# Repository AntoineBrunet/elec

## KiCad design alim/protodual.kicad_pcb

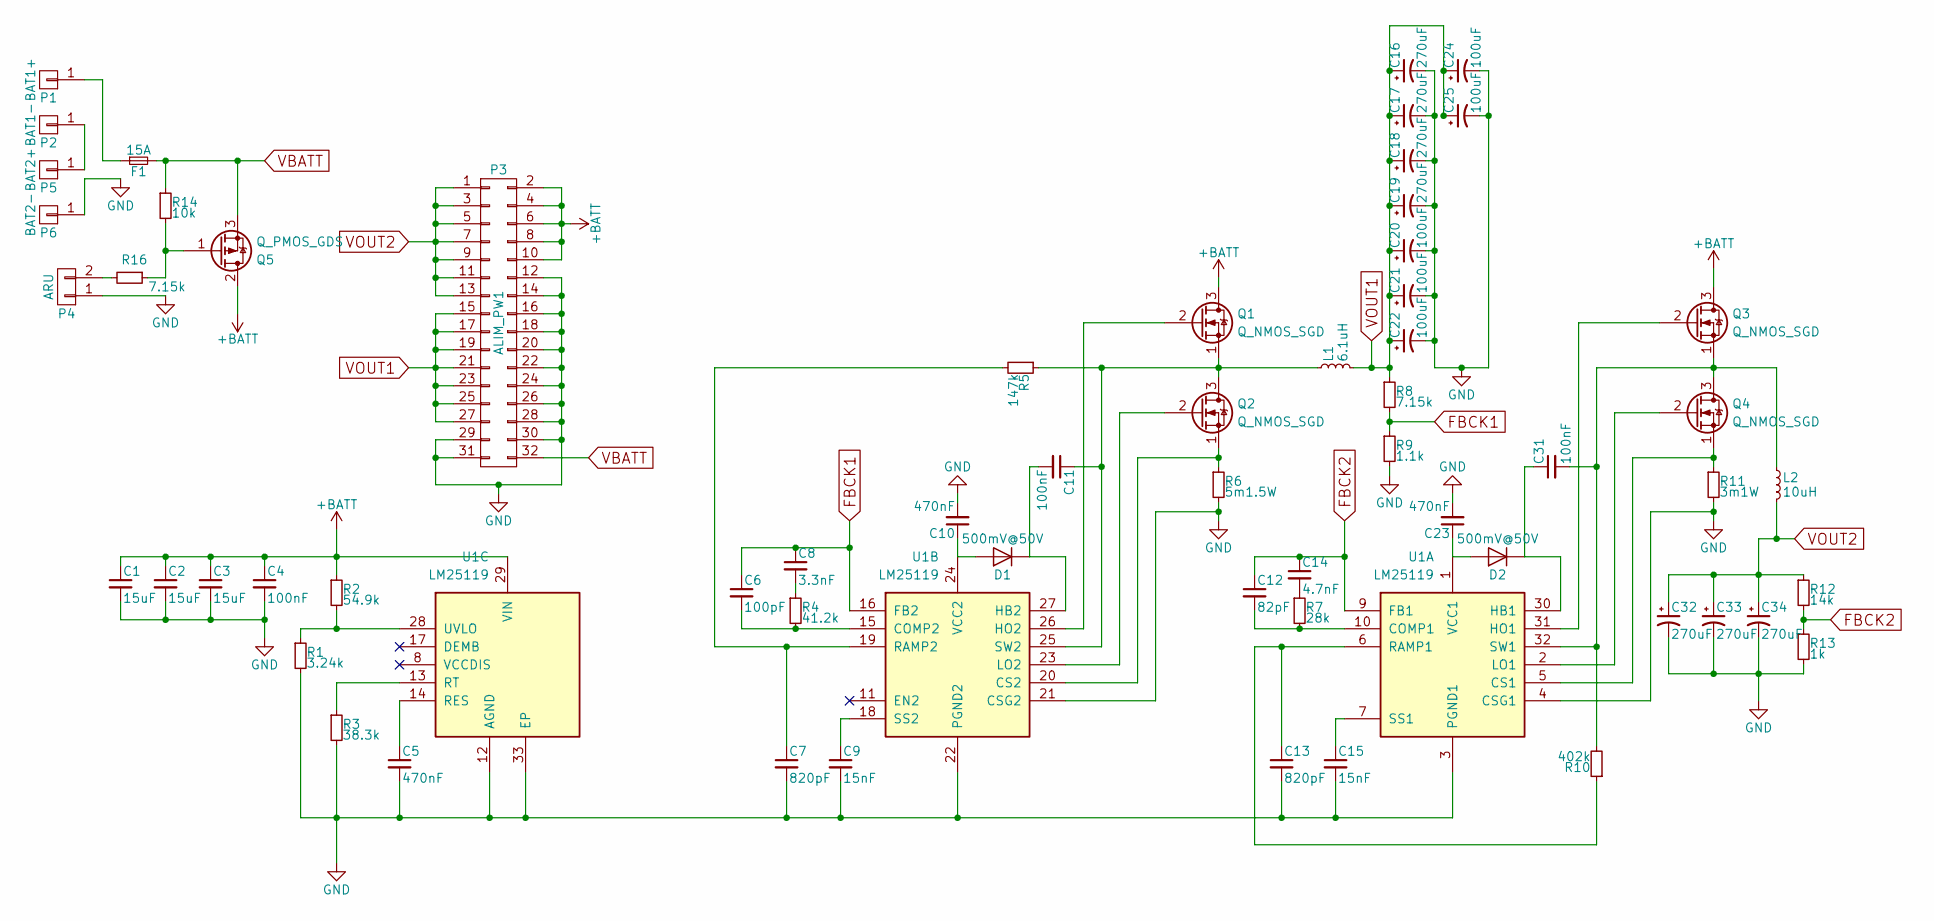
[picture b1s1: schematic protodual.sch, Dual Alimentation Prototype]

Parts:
C1, C2, C3: 15uF; C_2220_HandSoldering
C4, C11, C31: 100nF; C_0603_HandSoldering
C5: 470nF; C_1206_HandSoldering
C6: 100pF; C_0603_HandSoldering
C7, C13: 820pF; C_0603_HandSoldering
C8: 3.3nF; C_0603_HandSoldering
C9, C15: 15nF; C_0805_HandSoldering
C10, C23: 470nF; C_0603_HandSoldering
C12: 82pF; C_0603_HandSoldering
C14: 4.7nF; C_0603_HandSoldering
C16, C17, C18, C19, C32, C33, C34: 270uF; c_elec_6.3x7.7
C20, C21, C22, C24, C25: 100uF; Tantalum_Case-B_EIA-3528-21_Hand
D1, D2: 500mV@50V; D_0805
F1: 15A; Fuseholder5x20_horiz_SemiClosed_Casing10x25mm
L1: 6.1uH; Inductor_Wurth_HCI-1365
L2: 10uH; Inductor_Wurth_HCI-1365
P1: BAT1+; WireConnection_2.50mm
P2: BAT1-; WireConnection_2.50mm
P3: ALIM_PW1; Pin_Header_Straight_2x16
P4: ARU; Socket_Strip_Straight_1x02
P5: BAT2+; WireConnection_2.50mm
P6: BAT2-; WireConnection_2.50mm
Q1, Q2, Q3, Q4: Q_NMOS_SGD; TDSON8_MOSFET
Q5: Q_PMOS_GDS; SOT-428
R1: 3.24k; R_0603_HandSoldering
R2: 54.9k; R_0603_HandSoldering
R3: 38.3k; R_0603_HandSoldering
R4: 41.2k; R_0603_HandSoldering
R5: 147k; R_0603_HandSoldering
R6: 5m1.5W; R_2010_HandSoldering
R7: 28k; R_0603_HandSoldering
R8, R16: 7.15k; R_0603_HandSoldering
R9: 1.1k; R_0603_HandSoldering
R10: 402k; R_0603_HandSoldering
R11: 3m1W; R_2010_HandSoldering
R12: 14k; R_0603_HandSoldering
R13: 1k; R_0603_HandSoldering
R14: 10k; R_0603_HandSoldering
U1: LM25119; QFN-32-1EP_5x5mm_Pitch0.5mm

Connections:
+BATT: C1.1, C2.1, C3.1, C4.1, P3.2, P3.4, P3.6, P3.8, P3.10, Q1.3 (D), Q3.3 (D), Q5.2 (D), R2.1, U1.29 (VIN)
FBCK1: C6.1, C8.1, R8.2, R9.1, U1.16 (FB2)
FBCK2: C12.1, C14.1, R12.2, R13.1, U1.9 (FB1)
GND: C1.2, C2.2, C3.2, C4.2, C5.2, C7.2, C9.2, C10.2, C13.2, C15.2, C16.2, C17.2, C18.2, C19.2, C20.2, C21.2, C22.2, C23.2, C24.2, C25.2, C32.2, C33.2, C34.2, P3.12, P3.14, P3.16, P3.18, P3.20, P3.22, P3.24, P3.26, P3.28, P3.29, P3.30, P3.31, P4.1, P6.1, R1.2, R3.2, R6.2, R9.2, R11.2, R13.2, U1.3 (PGND1), U1.4 (CSG1), U1.12 (AGND), U1.21 (CSG2), U1.22 (PGND2), U1.33 (EP)
unnamed: C5.1, U1.14 (RES)
unnamed: C6.2, R4.2, U1.15 (COMP2)
unnamed: C7.1, R5.2, U1.19 (RAMP2)
unnamed: C8.2, R4.1
unnamed: C9.1, U1.18 (SS2)
unnamed: C10.1, D1.2 (A), U1.24 (VCC2)
unnamed: C11.1, L1.1, Q1.1 (S), Q2.3 (D), R5.1, U1.25 (SW2)
unnamed: C11.2, D1.1 (K), U1.27 (HB2)
unnamed: C12.2, R7.2, U1.10 (COMP1)
unnamed: C13.1, R10.1, U1.6 (RAMP1)
unnamed: C14.2, R7.1
unnamed: C15.1, U1.7 (SS1)
unnamed: C23.1, D2.2 (A), U1.1 (VCC1)
unnamed: C31.1, D2.1 (K), U1.30 (HB1)
unnamed: C31.2, L2.1, Q3.1 (S), Q4.3 (D), R10.2, U1.32 (SW1)
unnamed: F1.1, P1.1
unnamed: P2.1, P5.1
unnamed: P4.2, R16.2
unnamed: Q1.2 (G), U1.26 (HO2)
unnamed: Q2.1 (S), R6.1, U1.20 (CS2)
unnamed: Q2.2 (G), U1.23 (LO2)
unnamed: Q3.2 (G), U1.31 (HO1)
unnamed: Q4.1 (S), R11.1, U1.5 (CS1)
unnamed: Q4.2 (G), U1.2 (LO1)
unnamed: Q5.1 (G), R14.2, R16.1
unnamed: R1.1, R2.2, U1.28 (UVLO)
unnamed: R3.1, U1.13 (RT)
VBATT: F1.2, P3.32, Q5.3 (S), R14.1
VOUT1: C16.1, C17.1, C18.1, C19.1, C20.1, C21.1, C22.1, C24.1, C25.1, L1.2, P3.15, P3.17, P3.19, P3.21, P3.23, P3.25, P3.27, R8.1
VOUT2: C32.1, C33.1, C34.1, L2.2, P3.1, P3.3, P3.5, P3.7, P3.9, P3.11, P3.13, R12.1

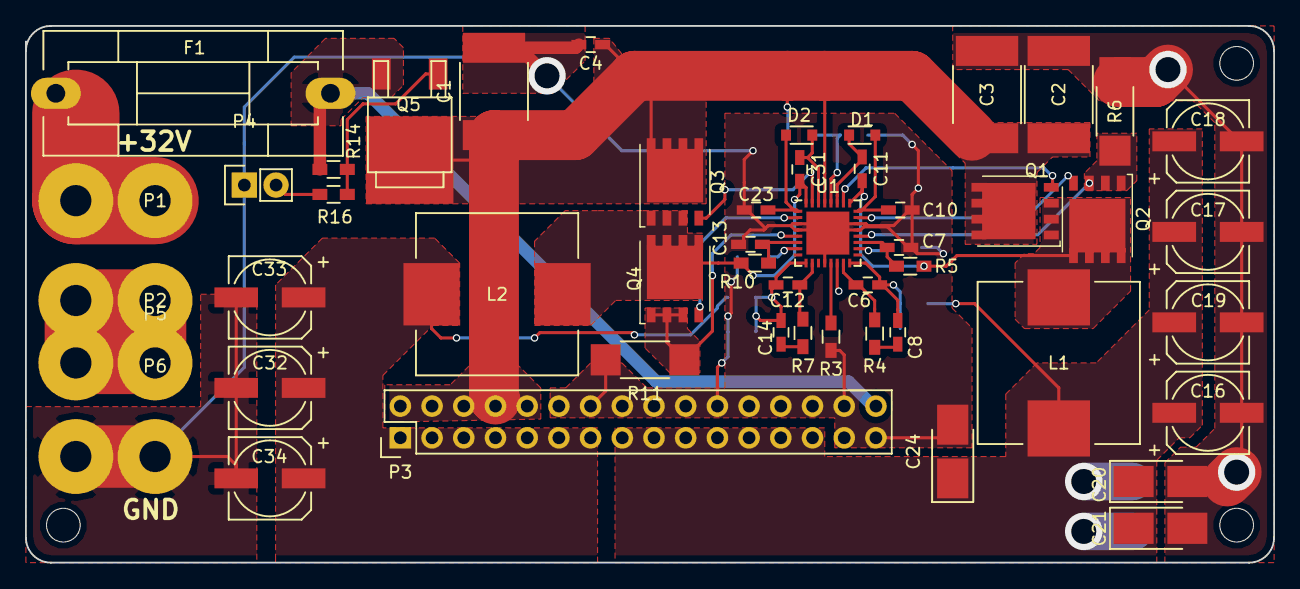
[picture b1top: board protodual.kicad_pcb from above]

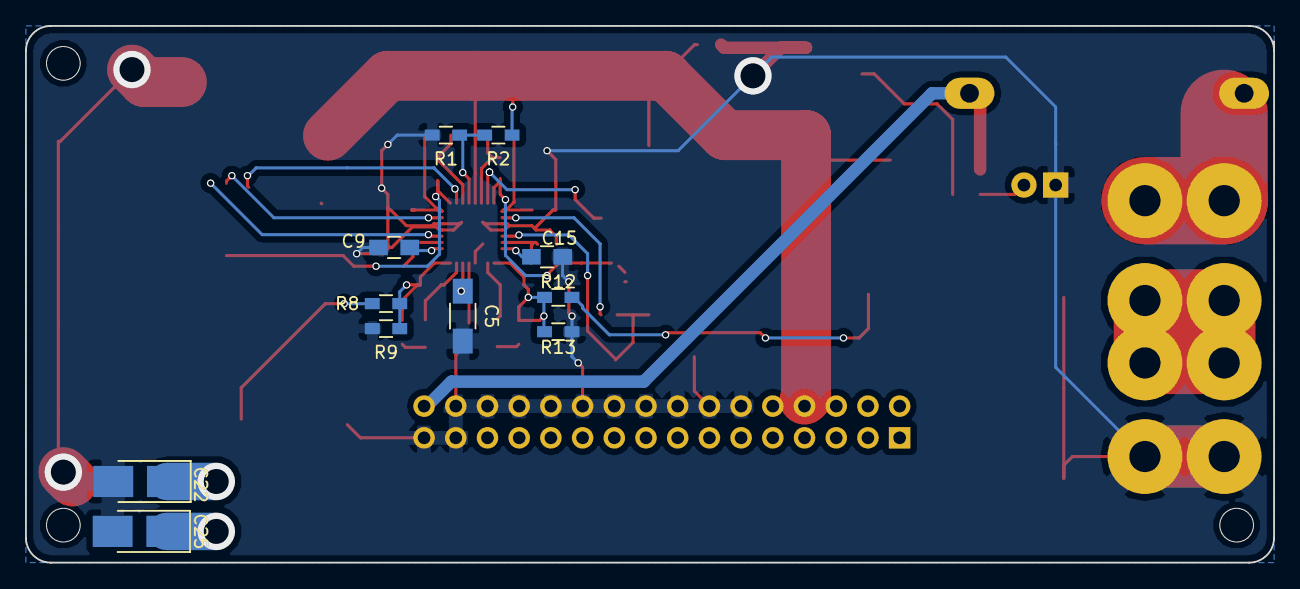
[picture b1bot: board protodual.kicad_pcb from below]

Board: 2 copper layers, 100.0 x 43.0 mm, 61 parts (11 on the bottom side), 34 nets.

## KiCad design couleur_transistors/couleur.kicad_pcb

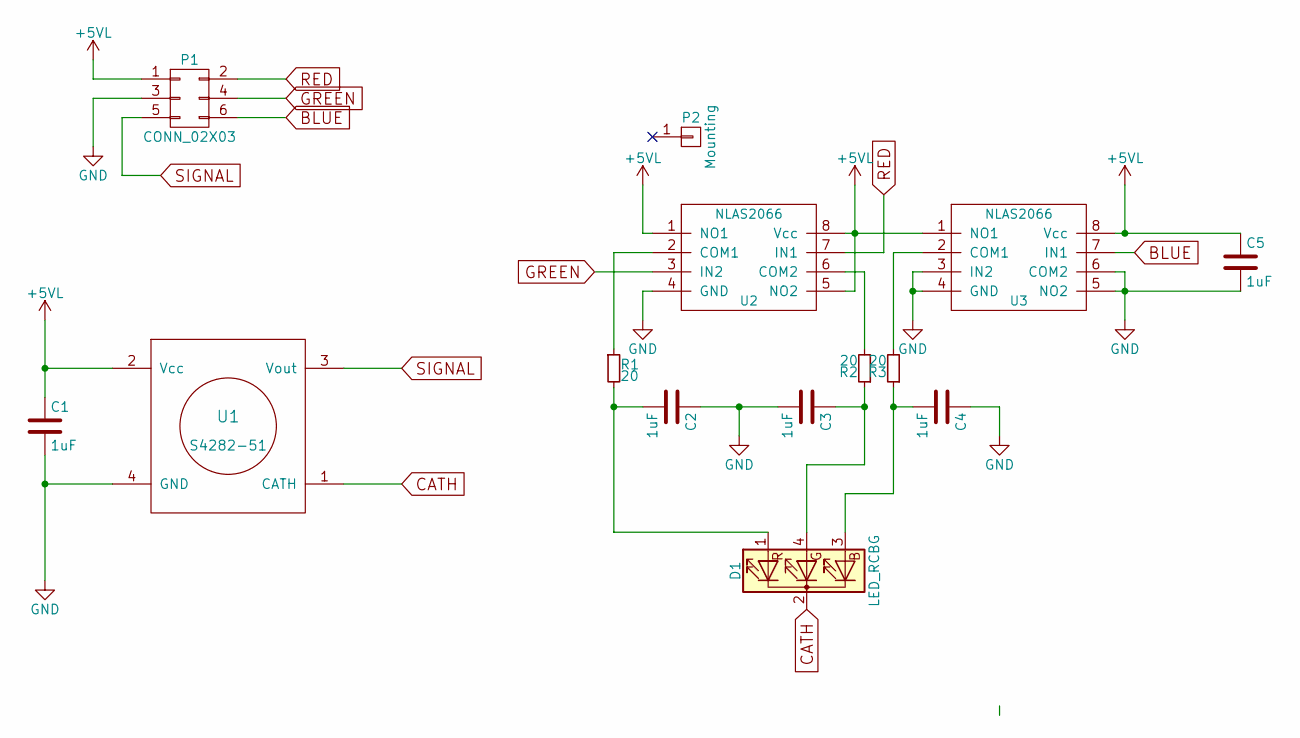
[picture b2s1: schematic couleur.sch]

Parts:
C1, C2, C3, C4, C5: 1uF; C_0603_HandSoldering
D1: LED_RCBG; LED-RGB-5MM_Common_Cathode
P1: CONN_02X03; Pin_Header_Straight_2x03
P2: Mounting; MountingHole_3.2mm_M3_Pad
R1, R2, R3: 20; R_0603_HandSoldering
U1: S4282-51
U2, U3: NLAS2066; TSSOP-8_3x3mm_Pitch0.65mm

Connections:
+5VL: C1.1, C5.1, P1.1, U1.2 (Vcc), U2.1 (NO1), U2.5 (NO2), U2.8 (Vcc), U3.1 (NO1), U3.8 (Vcc)
BLUE: P1.6, U3.7 (IN1)
CATH: D1.2 (K), U1.1 (CATH)
GND: C1.2, C2.1, C3.2, C4.1, C5.2, P1.3, U1.4 (GND), U2.4 (GND), U3.3 (IN2), U3.4 (GND), U3.5 (NO2), U3.6 (COM2)
GREEN: P1.4, U2.3 (IN2)
unnamed: C2.2, D1.1 (RA), R1.2
unnamed: C3.1, D1.4 (GA), R2.1
unnamed: C4.2, D1.3 (BA), R3.1
unnamed: R1.1, U2.2 (COM1)
unnamed: R2.2, U2.6 (COM2)
unnamed: R3.2, U3.2 (COM1)
RED: P1.2, U2.7 (IN1)
SIGNAL: P1.5, U1.3 (Vout)

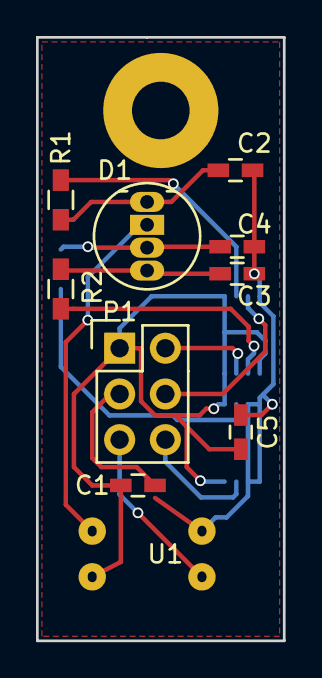
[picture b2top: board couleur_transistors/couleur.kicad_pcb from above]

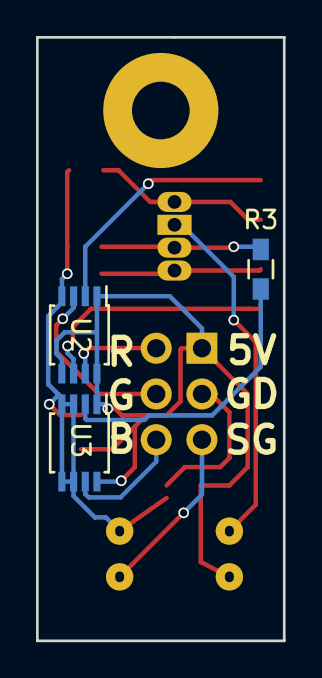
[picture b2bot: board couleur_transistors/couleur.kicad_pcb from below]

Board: 2 copper layers, 13.7 x 33.5 mm, 14 parts (3 on the bottom side), 13 nets.

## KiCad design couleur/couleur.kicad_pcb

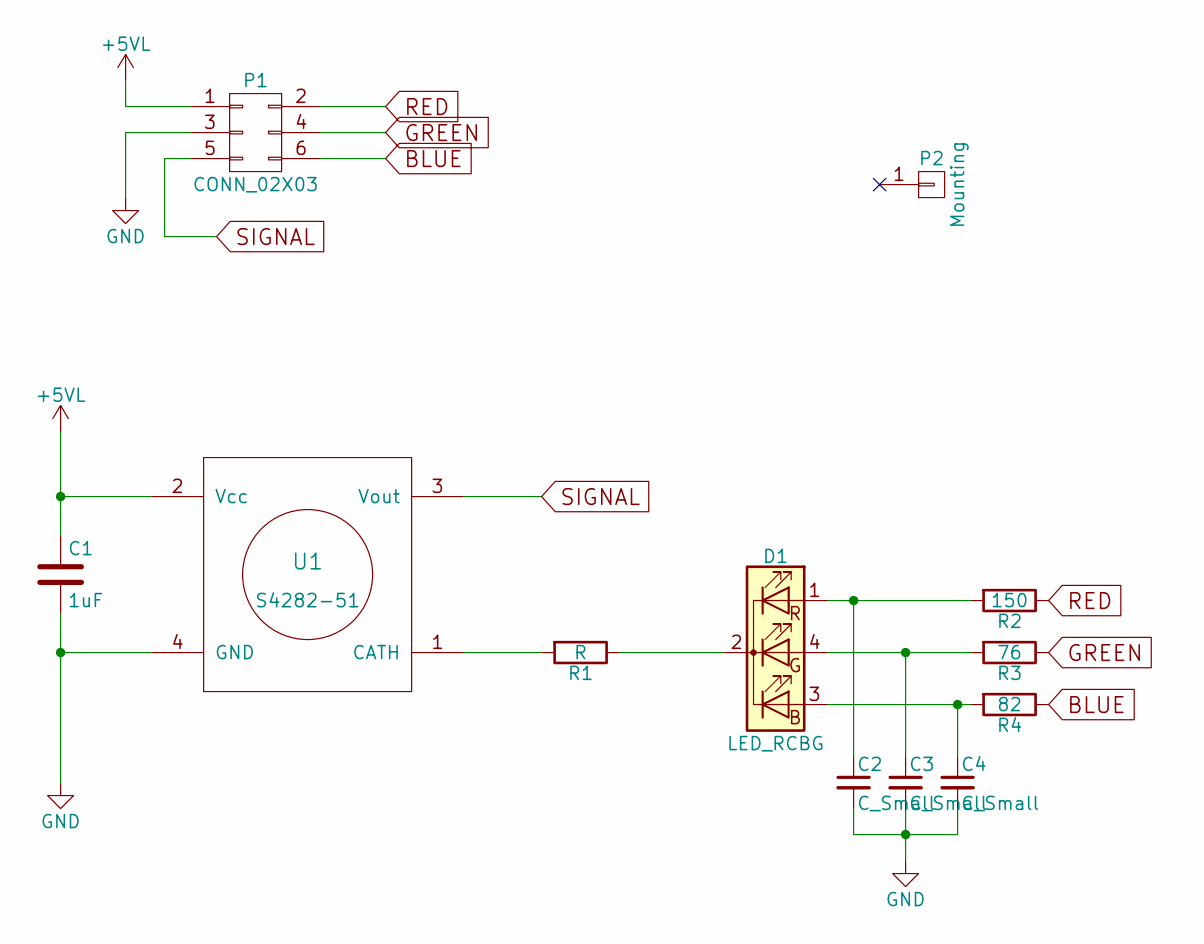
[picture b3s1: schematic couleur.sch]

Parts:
C1: 1uF; C_0603_HandSoldering
C2, C3, C4: C_Small; C_0603_HandSoldering
D1: LED_RCBG; LED-RGB-5MM_Common_Cathode
P1: CONN_02X03; Pin_Header_Straight_2x03
P2: Mounting; MountingHole_3.2mm_M3_Pad
R1: R; R_0603_HandSoldering
R2: 150; R_0603_HandSoldering
R3: 76; R_0603_HandSoldering
R4: 82; R_0603_HandSoldering
U1: S4282-51

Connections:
+5VL: C1.1, P1.1, U1.2 (Vcc)
BLUE: P1.6, R4.1
GND: C1.2, C2.2, C3.2, C4.2, P1.3, U1.4 (GND)
GREEN: P1.4, R3.1
unnamed: C2.1, D1.1 (RA), R2.2
unnamed: C3.1, D1.4 (GA), R3.2
unnamed: C4.1, D1.3 (BA), R4.2
unnamed: D1.2 (K), R1.1
unnamed: R1.2, U1.1 (CATH)
RED: P1.2, R2.1
SIGNAL: P1.5, U1.3 (Vout)

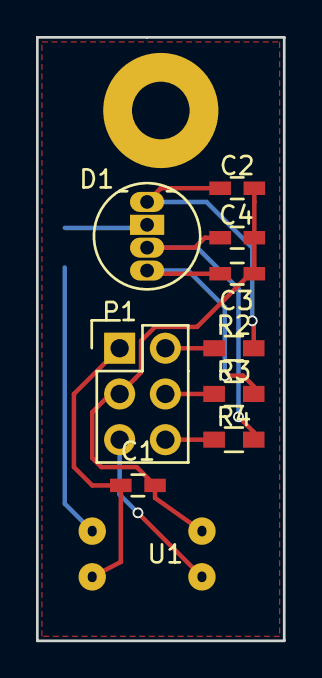
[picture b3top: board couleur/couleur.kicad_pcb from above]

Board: 2 copper layers, 13.7 x 33.5 mm, 12 parts (1 on the bottom side), 11 nets.

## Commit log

2018-01-18 Alim
2018-01-20 Proto dual
2018-02-06 MAJ alim + couleur
2018-02-06 Couleur transistors
2018-02-08 COuleur avec transistors
2018-02-11 Alim finale?
2018-02-18 ALim a grosse piste
2018-02-18 Couleur
2018-04-03 Alim protodual
2018-04-03 alims
